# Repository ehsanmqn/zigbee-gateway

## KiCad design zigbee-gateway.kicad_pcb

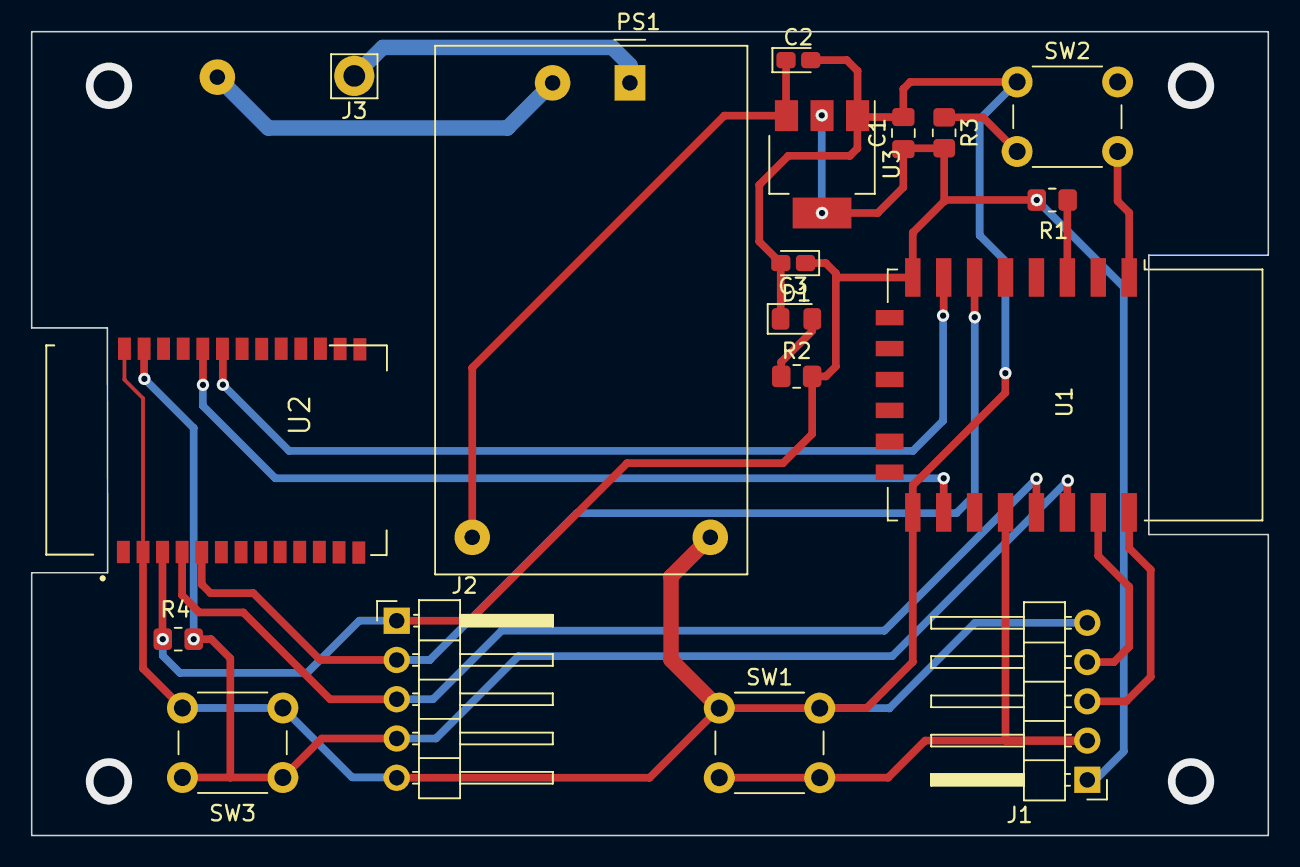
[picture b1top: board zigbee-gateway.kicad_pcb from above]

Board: 2 copper layers, 80.0 x 52.0 mm, 18 parts (0 on the bottom side), 15 nets.

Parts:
C1: 0.1uF; C_0805_2012Metric_Pad1.18x1.45mm_HandSolder
C2, C3: 22uF; CP_EIA-1608-10_AVX-L_Pad1.25x1.05mm_HandSolder
D1: RED; LED_0805_2012Metric_Pad1.15x1.40mm_HandSolder
J1, J2: Conn_01x04; PinHeader_1x05_P2.54mm_Horizontal
J3: Conn_01x02_Male; Pin_D1.4mm_L8.5mm_W2.8mm_FlatFork
PS1: HLK-PM01; Converter_ACDC_HiLink_HLK-PMxx
R1, R3, R4: 10K; R_0805_2012Metric_Pad1.20x1.40mm_HandSolder
R2: 2.2K; R_0805_2012Metric_Pad1.20x1.40mm_HandSolder
SW1, SW2, SW3: SW_Push; SW_PUSH_6mm
U1: ESP-12E
U2: CC2530-A1_Module; cc2530-a2
U3: AZ1117-3.3; SOT-223-3_TabPin2

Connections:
+3V3: C1.1, C3.1, J1.1, J2.1, R1.1, R2.2, R3.2, R4.2, U1.8 (VCC), U2.24 (VCC), U3.2 (VO)
+5V: C2.1, PS1.4 (+Vout), U3.3 (VI)
D1: J2.4, R4.1, SW3.2, U1.20 (GPIO5), U2.2 (RESTE)
D2: J2.3, U1.19 (GPIO4), U2.23 (P2.2)
D6: J2.2, U1.6 (GPIO12), U2.22 (P2.1)
D7: U1.7 (GPIO13), U2.6 (P0.3)
D8: U1.16 (GPIO15), U2.5 (P0.2)
GND: C1.2, C2.2, C3.2, D1.1 (K), J1.5, J2.5, PS1.3 (-Vout), SW1.1, SW2.1, SW3.1, U1.15 (GND), U2.1 (GND), U2.25 (GND), U3.1 (GND)
GPIO0: J1.2, SW1.2, U1.18 (GPIO0)
unnamed: D1.2 (A), R2.1
unnamed: J3.1, PS1.1 (AC/L)
unnamed: R1.2, U1.3 (EN)
RST: R3.1, SW2.2, U1.1 (~RST)
RX: J1.4, U1.21 (GPIO3/RXD)
TX: J1.3, U1.22 (GPIO1/TXD)

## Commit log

2022-04-03 ome changes performed for adding switching to the board
